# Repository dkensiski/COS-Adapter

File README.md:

# COS Adapter V2

The [Kenwood TK-981](https://www.kw902.com/981generalinfo.html) radio's COS output
does not go suffciently low to reliably trigger the
[Arcom RC210](https://www.arcomcontrollers.com/index.php?Itemid=524&route=product/product&product_id=33)
controller's COS input, so Jim (K6KCP) designed this comparator circuit to perform
the trick.

## Features

* Trigger pot to adjust the COS trigger level
* Relay to close COS outut (normally open)
* Audio circuitry (thanks Steve W6KCS) to adjust and filter the audio between
  the devices.  Components can be added or jumpered to suit.
* Mounting holes for a small [project box](https://amazon.com/dp/B07D23C962/)
  or inside the [RC210 enclosure](https://www.arcomcontrollers.com/index.php?Itemid=524&route=product/product&product_id=32)

## Parts list

| Part   | Value | Notes |
| ------ | ----- | ----- |
| **C1** | .01 | |
| **D1** | LED | |
| **D2** | 1N400X | |
| **J1** | 2-pin JMT male | |
| **J2** | 2-pin JMT male | |
| **J3** | RCA phono | Cliff FC68400, Same Sky RCJ-02x, or equiv |
| **J8** | 3-pin JMT male | |
| **J9** | 3-pin JMT male | |
| **K1** | DIP Mini Relay | Littlefuse HE721C1200 |
| **Q1** | 2N3906 | |
| **R1** | 4700 ohm | |
| **R2** | 1000 ohm | |
| **R3** | 50K | optional; replace with wire if not used |
| **R4** | 50K | optional; replace with wire if not used |
| **RV1** | 50K trim pot | Bourns style 3386P or 3386V |
| **RV2** | 10K trim pot | |
| **RV3** | 10K trim pot | |
| **U1** | LM741 | |

## 3-D rendering

## PCB Layout

## Schematic

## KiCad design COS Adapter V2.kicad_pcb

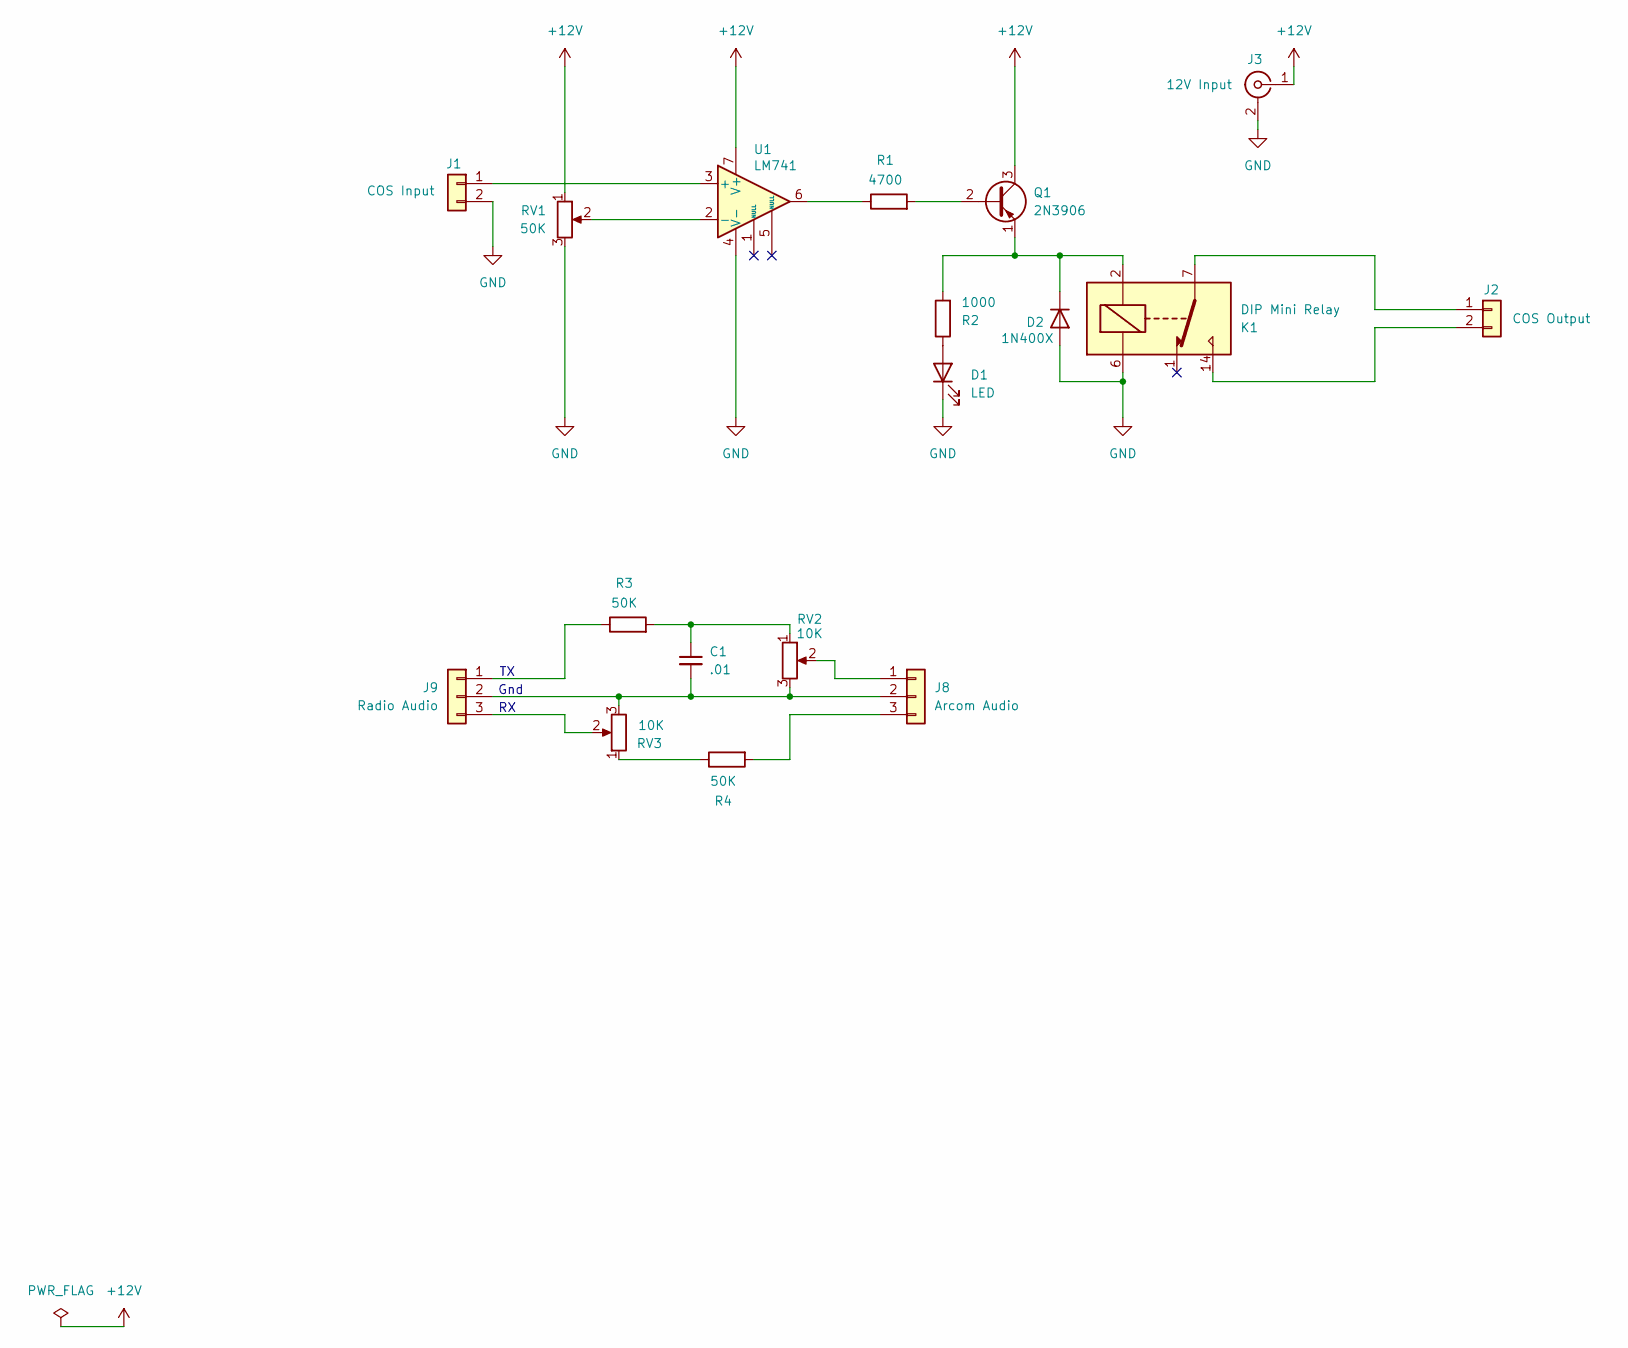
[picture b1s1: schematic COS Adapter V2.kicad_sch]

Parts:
C1: .01; C_Axial_L5.1mm_D3.1mm_P7.50mm_Horizontal_BIG_FEET
D1: LED; LED_D3.0mm
D2: 1N400X; D_A-405_P7.62mm_Horizontal
J1: COS Input; JST_EH_B2B-EH-A_1x02_P2.50mm_Vertical
J2: COS Output; JST_EH_B2B-EH-A_1x02_P2.50mm_Vertical
J3: 12V Input; CUI_RCJ-025
J8: Arcom Audio; JST_EH_B3B-EH-A_1x03_P2.50mm_Vertical
J9: Radio Audio; JST_EH_B3B-EH-A_1x03_P2.50mm_Vertical
K1: DIP Mini Relay; Relay_StandexMeder_DIP_LowProfile
Q1: 2N3906; TO-92_Inline
R1: 4700; R_Axial_DIN0204_L3.6mm_D1.6mm_P7.62mm_Horizontal
R2: 1000; R_Axial_DIN0204_L3.6mm_D1.6mm_P7.62mm_Horizontal
R3, R4: 50K; R_Axial_DIN0204_L3.6mm_D1.6mm_P7.62mm_Horizontal_BIG_FEET
RV1: 50K; Potentiometer_Runtron_RM-063_Horizontal
RV2, RV3: 10K; Potentiometer_Runtron_RM-063_Horizontal
U1: LM741; DIP-8_W7.62mm_LongPads

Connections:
+12V: J3.1 (In), Q1.3 (C), RV1.1, U1.7 (V+)
GND: D1.1 (K), D2.2 (A), J1.2, J3.2 (Ext), K1.6, RV1.3, U1.4 (V-)
unnamed: C1.1, R3.2, RV2.1
unnamed: D1.2 (A), R2.1
unnamed: D2.1 (K), K1.2, Q1.1 (E), R2.2
unnamed: J1.1, U1.3 (+)
unnamed: J2.1, K1.7, K1.8
unnamed: J2.2, K1.14
unnamed: J8.1, RV2.2
unnamed: C1.2, J8.2, J9.2, RV2.3, RV3.3
unnamed: J8.3, R4.2
unnamed: J9.1, R3.1
unnamed: J9.3, RV3.2
unnamed: Q1.2 (B), R1.2
unnamed: R1.1, U1.6
unnamed: R4.1, RV3.1
unnamed: RV1.2, U1.2 (-)

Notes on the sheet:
Gnd

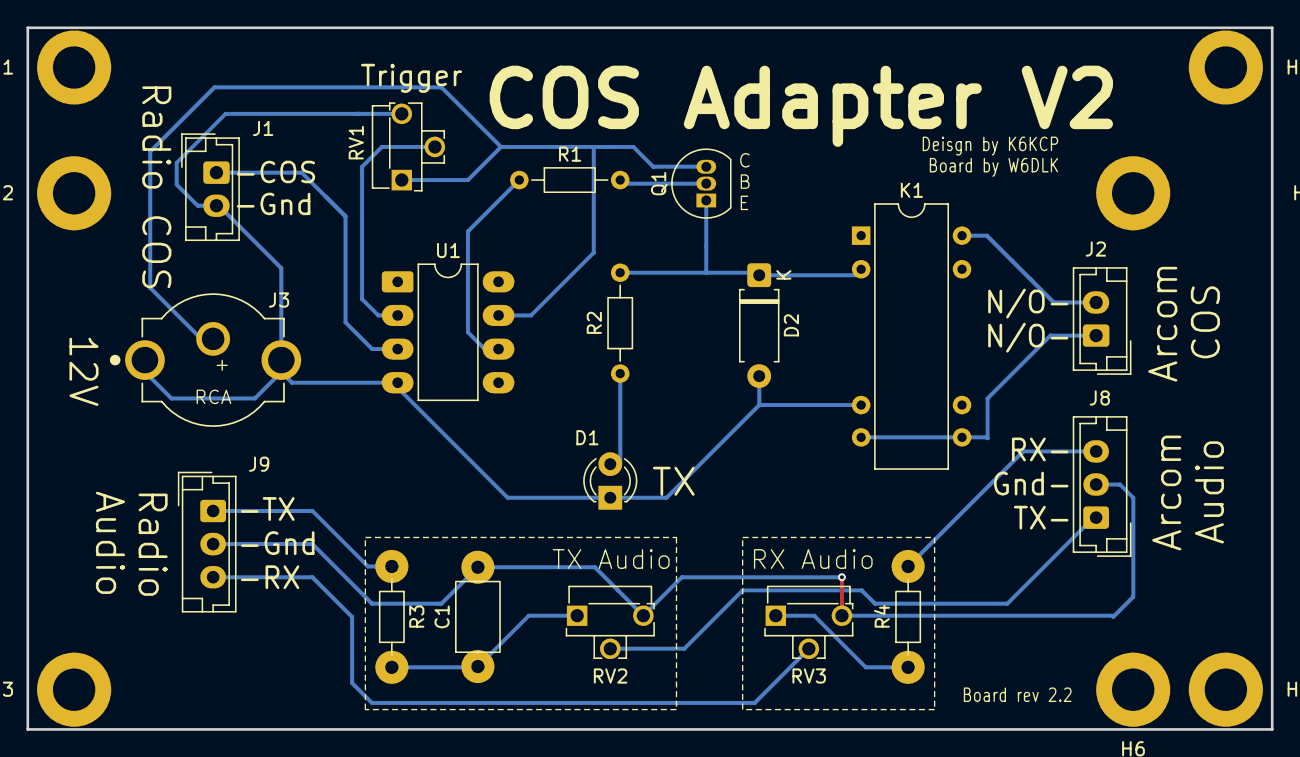
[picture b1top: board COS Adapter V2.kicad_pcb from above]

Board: 2 copper layers, 94.0 x 53.0 mm, 25 parts (0 on the bottom side), 17 nets.

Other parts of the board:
H1, H2, H3, H4, H5, H6, H7: MountingHole_3.2mm_M3_DIN965_Pad

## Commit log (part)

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2026-01-13 added big pads
2026-01-13 add pics
2026-01-14 add .gitignore
2026-01-14 add Arcom mounting holes
2026-01-17 fabrication export for v1.0 board
2026-01-17 fill in the foil
2026-01-17 add README
2026-01-17 added some words and pics
2026-01-17 fixed file paths
2026-01-17 add links to things
2026-01-25 added parts list
2026-01-25 convert parts list to table
2026-01-25 add header to table
2026-01-25 clean up parts table
2026-01-25 added parts notes
2026-01-25 updated notes
2026-03-08 v2.2: fix diode polarity
